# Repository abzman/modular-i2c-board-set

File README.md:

# modular-i2c-board-set
boards designed to be used together to create a modular control system

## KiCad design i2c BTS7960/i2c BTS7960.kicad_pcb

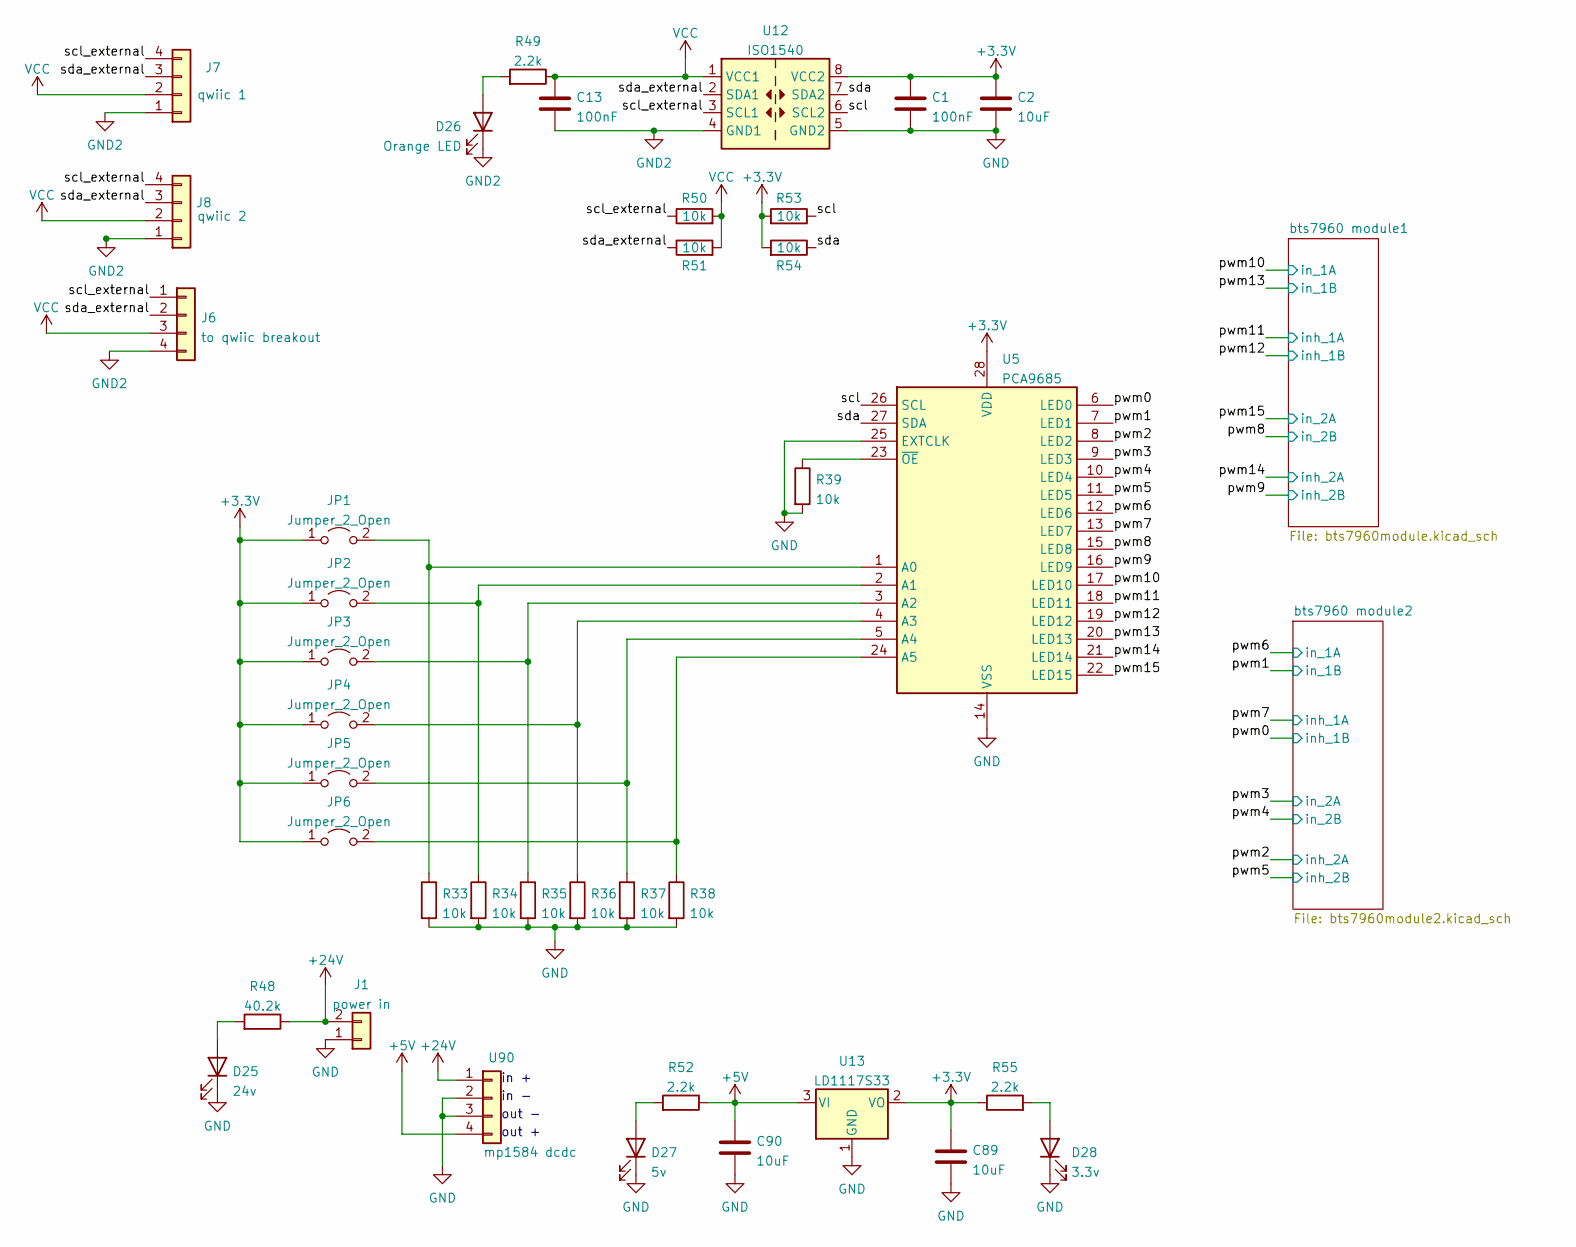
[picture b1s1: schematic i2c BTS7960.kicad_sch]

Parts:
C1, C13: 100nF; C_0603_1608Metric
C2: 10uF; C_0603_1608Metric
C89, C90: 10uF; C_1206_3216Metric
D25: 24v; LED_0603_1608Metric
D26: Orange LED; LED_0603_1608Metric
D27: 5v; LED_0603_1608Metric
D28: 3.3v; LED_0603_1608Metric
J1: power in; TerminalBlock_Phoenix_MKDS-1,5-2_1x02_P5.00mm_Horizontal
J6: to qwiic breakout; PinHeader_1x04_P2.54mm_Vertical
J7: qwiic 1; JST_SH_SM04B-SRSS-TB_1x04-1MP_P1.00mm_Horizontal
J8: qwiic 2; JST_SH_SM04B-SRSS-TB_1x04-1MP_P1.00mm_Horizontal
JP1, JP2, JP3, JP4, JP5: Jumper_2_Open; SolderJumper-2_P1.3mm_Open_RoundedPad1.0x1.5mm
JP6: Jumper_2_Open; SolderJumper-2_P1.3mm_Bridged_RoundedPad1.0x1.5mm
R33, R34, R35, R36, R37, R38, R39, R50, R51, R53, R54: 10k; R_0603_1608Metric
R48: 40.2k; R_0603_1608Metric
R49, R52, R55: 2.2k; R_0603_1608Metric
U5: PCA9685; TSSOP-28_4.4x9.7mm_P0.65mm
U12: ISO1540; SOIC-8_3.9x4.9mm_P1.27mm
U13: LD1117S33; SOT-223-3_TabPin2
U90: mp1584 dcdc; MP1584_buck_module

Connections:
+3V3: C1.1, C2.1, C89.1, JP1.1 (A), JP2.1 (A), JP3.1 (A), JP4.1 (A), JP5.1 (A), JP6.1 (A), R53.2, R54.2, R55.1, U5.28 (VDD), U12.8 (VCC2), U13.2 (VO)
+5V: C90.1, R52.1, U13.3 (VI), U90.4; also elsewhere on the board
+24V: J1.2, R48.1, U90.1; also elsewhere on the board
/pwm0: U5.6 (LED0); also elsewhere on the board
/pwm1: U5.7 (LED1); also elsewhere on the board
/pwm2: U5.8 (LED2); also elsewhere on the board
/pwm3: U5.9 (LED3); also elsewhere on the board
/pwm4: U5.10 (LED4); also elsewhere on the board
/pwm5: U5.11 (LED5); also elsewhere on the board
/pwm6: U5.12 (LED6); also elsewhere on the board
/pwm7: U5.13 (LED7); also elsewhere on the board
/pwm8: U5.15 (LED8); also elsewhere on the board
/pwm9: U5.16 (LED9); also elsewhere on the board
/pwm10: U5.17 (LED10); also elsewhere on the board
/pwm11: U5.18 (LED11); also elsewhere on the board
/pwm12: U5.19 (LED12); also elsewhere on the board
/pwm13: U5.20 (LED13); also elsewhere on the board
/pwm14: U5.21 (LED14); also elsewhere on the board
/pwm15: U5.22 (LED15); also elsewhere on the board
/scl: R53.1, U5.26 (SCL), U12.6 (SCL2)
/scl_external: J6.1, J7.4, J8.4, R50.1, U12.3 (SCL1)
/sda: R54.1, U5.27 (SDA), U12.7 (SDA2)
/sda_external: J6.2, J7.3, J8.3, R51.1, U12.2 (SDA1)
GND: C1.2, C2.2, C89.2, C90.2, D25.1 (K), D27.1 (K), D28.1 (K), J1.1, J7.MP, J8.MP, R33.2, R34.2, R35.2, R36.2, R37.2, R38.2, R39.2, U5.14 (VSS), U5.25 (EXTCLK), U12.5 (GND2), U13.1 (GND), U90.2, U90.3; also elsewhere on the board
GND2: C13.2, D26.1 (K), J6.4, J7.1, J8.1, U12.4 (GND1)
unnamed: D25.2 (A), R48.2
unnamed: D26.2 (A), R49.2
unnamed: D27.2 (A), R52.2
unnamed: D28.2 (A), R55.2
unnamed: JP1.2 (B), R33.1, U5.1 (A0)
unnamed: JP2.2 (B), R34.1, U5.2 (A1)
unnamed: JP3.2 (B), R35.1, U5.3 (A2)
unnamed: JP4.2 (B), R36.1, U5.4 (A3)
unnamed: JP5.2 (B), R37.1, U5.5 (A4)
unnamed: JP6.2 (B), R38.1, U5.24 (A5)
unnamed: R39.1, U5.23 (~OE)
VCC: C13.1, J6.3, J7.2, J8.2, R49.1, R50.2, R51.2, U12.1 (VCC1)

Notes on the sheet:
in +
out -
out +
in -

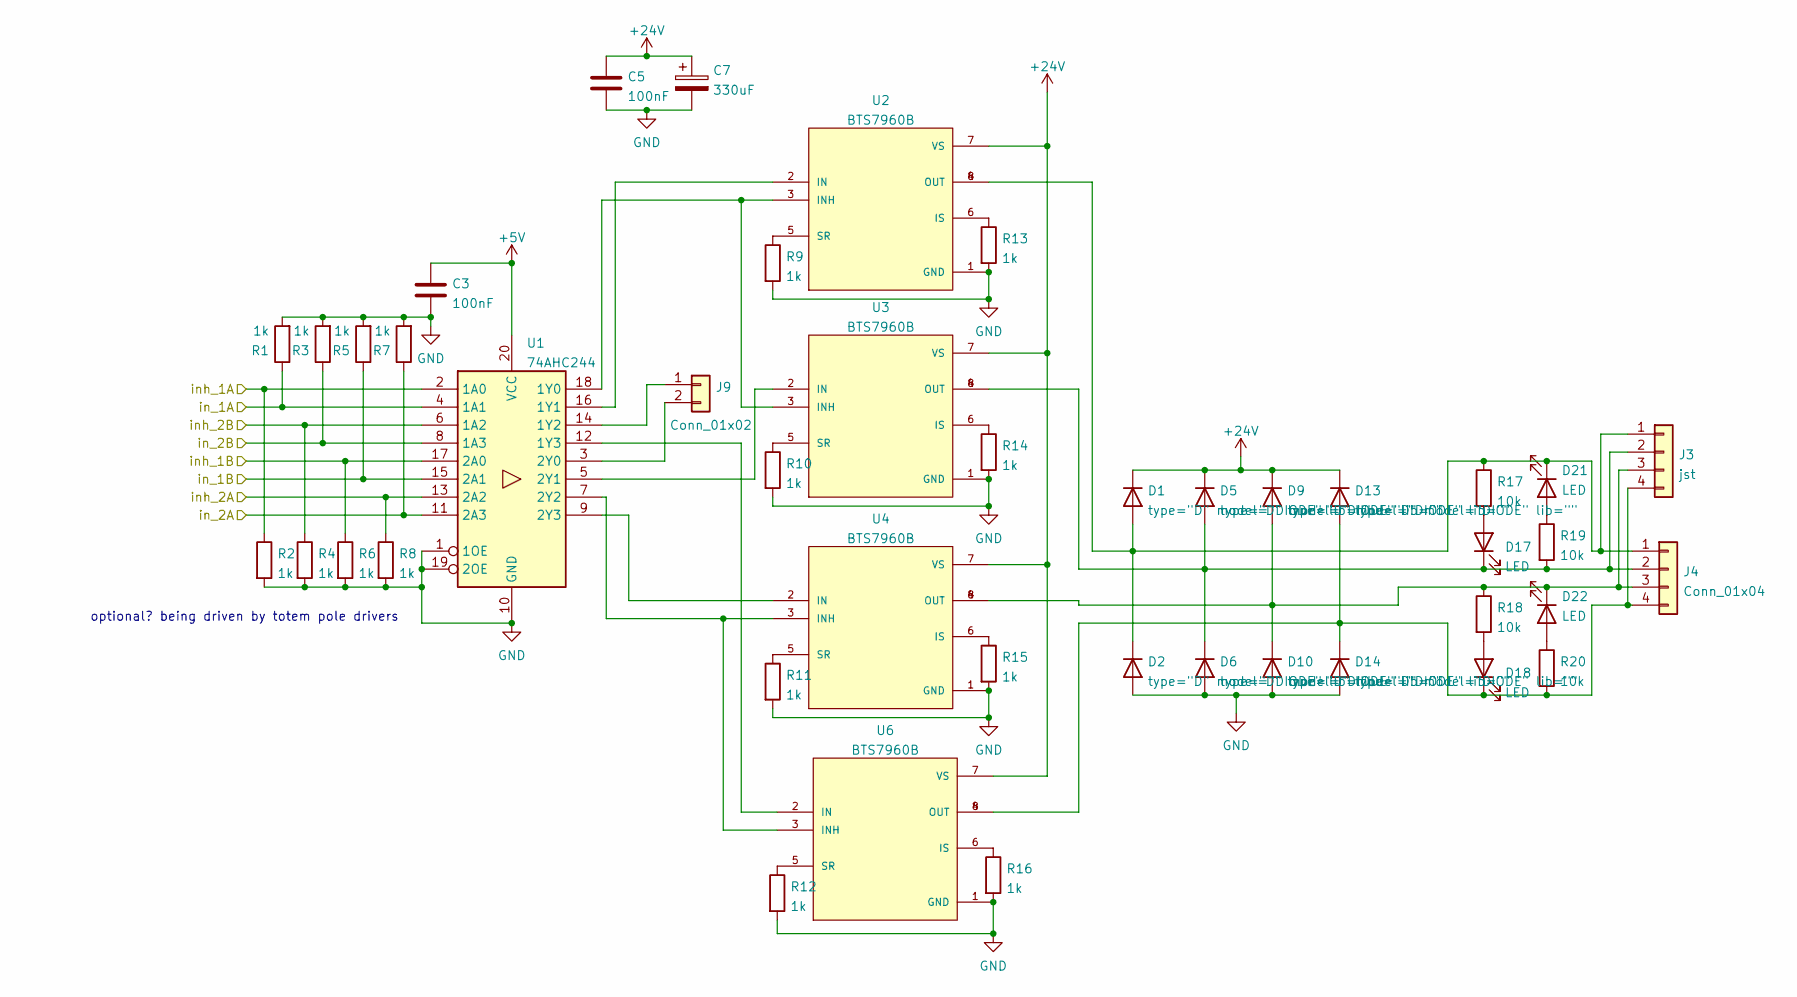
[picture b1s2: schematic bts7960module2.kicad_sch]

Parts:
C3, C5: 100nF; C_0603_1608Metric
C7: 330uF; CP_Radial_D10.0mm_P5.00mm
D1, D2, D5, D6, D9, D10, D13, D14: type="D" model="DIODE" lib=""; D_SMA
D17, D18, D21, D22: LED; LED_0603_1608Metric
J3: jst; JST_XH_B4B-XH-A_1x04_P2.50mm_Vertical
J4: Conn_01x04; TerminalBlock_Phoenix_MKDS-1,5-4_1x04_P5.00mm_Horizontal
J9: Conn_01x02; PinHeader_2x01_P2.54mm_Vertical
R1, R2, R3, R4, R5, R6, R7, R8, R9, R10, R11, R12, R13, R14, R15, R16: 1k; R_0603_1608Metric
R17, R18, R19, R20: 10k; R_0603_1608Metric
U1: 74AHC244; SOIC-20W_7.5x12.8mm_P1.27mm
U2, U3, U4, U6: BTS7960B; DPAK127P1490X440-8N; PARTREV 1.1

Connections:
+5V: C3.1, U1.20 (VCC); also elsewhere on the board
+24V: C5.1, C7.1, D1.2 (K), D5.2 (K), D9.2 (K), D13.2 (K), U2.7 (VS), U3.7 (VS), U4.7 (VS), U6.7 (VS); also elsewhere on the board
/pwm0: R6.1, U1.17 (2A0); also elsewhere on the board
/pwm1: R5.1, U1.15 (2A1); also elsewhere on the board
/pwm2: R8.1, U1.13 (2A2); also elsewhere on the board
/pwm3: R7.1, U1.11 (2A3); also elsewhere on the board
/pwm4: R3.1, U1.8 (1A3); also elsewhere on the board
/pwm5: R4.1, U1.6 (1A2); also elsewhere on the board
/pwm6: R1.1, U1.4 (1A1); also elsewhere on the board
/pwm7: R2.1, U1.2 (1A0); also elsewhere on the board
GND: C3.2, C5.2, C7.2, D2.1 (A), D6.1 (A), D10.1 (A), D14.1 (A), R1.2, R2.2, R3.2, R4.2, R5.2, R6.2, R7.2, R8.2, R9.2, R10.2, R11.2, R12.2, R13.2, R14.2, R15.2, R16.2, U1.1 (1OE), U1.10 (GND), U1.19 (2OE), U2.1 (GND), U3.1 (GND), U4.1 (GND), U6.1 (GND); also elsewhere on the board
unnamed: D1.1 (A), D2.2 (K), D21.1 (K), J3.1, J4.1, R17.1, U2.4 (OUT), U2.8 (OUT)
unnamed: D9.1 (A), D10.2 (K), D22.1 (K), J3.3, J4.3, R18.1, U4.4 (OUT), U4.8 (OUT)
unnamed: D13.1 (A), D14.2 (K), D18.1 (K), J3.4, J4.4, R20.2, U6.4 (OUT), U6.8 (OUT)
unnamed: D17.2 (A), R17.2
unnamed: D5.1 (A), D6.2 (K), D17.1 (K), J3.2, J4.2, R19.2, U3.4 (OUT), U3.8 (OUT)
unnamed: D18.2 (A), R18.2
unnamed: D21.2 (A), R19.1
unnamed: D22.2 (A), R20.1
unnamed: J9.1, U1.14 (1Y2)
unnamed: J9.2, U1.3 (2Y0)
unnamed: U1.18 (1Y0), U2.3 (INH), U3.3 (INH)
unnamed: U1.16 (1Y1), U2.2 (IN)
unnamed: U1.12 (1Y3), U6.2 (IN)
unnamed: U1.5 (2Y1), U3.2 (IN)
unnamed: U1.7 (2Y2), U4.3 (INH), U6.3 (INH)
unnamed: U1.9 (2Y3), U4.2 (IN)
unnamed: R13.1, U2.6 (IS)
unnamed: R9.1, U2.5 (SR)
unnamed: R14.1, U3.6 (IS)
unnamed: R10.1, U3.5 (SR)
unnamed: R15.1, U4.6 (IS)
unnamed: R11.1, U4.5 (SR)
unnamed: R16.1, U6.6 (IS)
unnamed: R12.1, U6.5 (SR)

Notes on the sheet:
optional? being driven by totem pole drivers

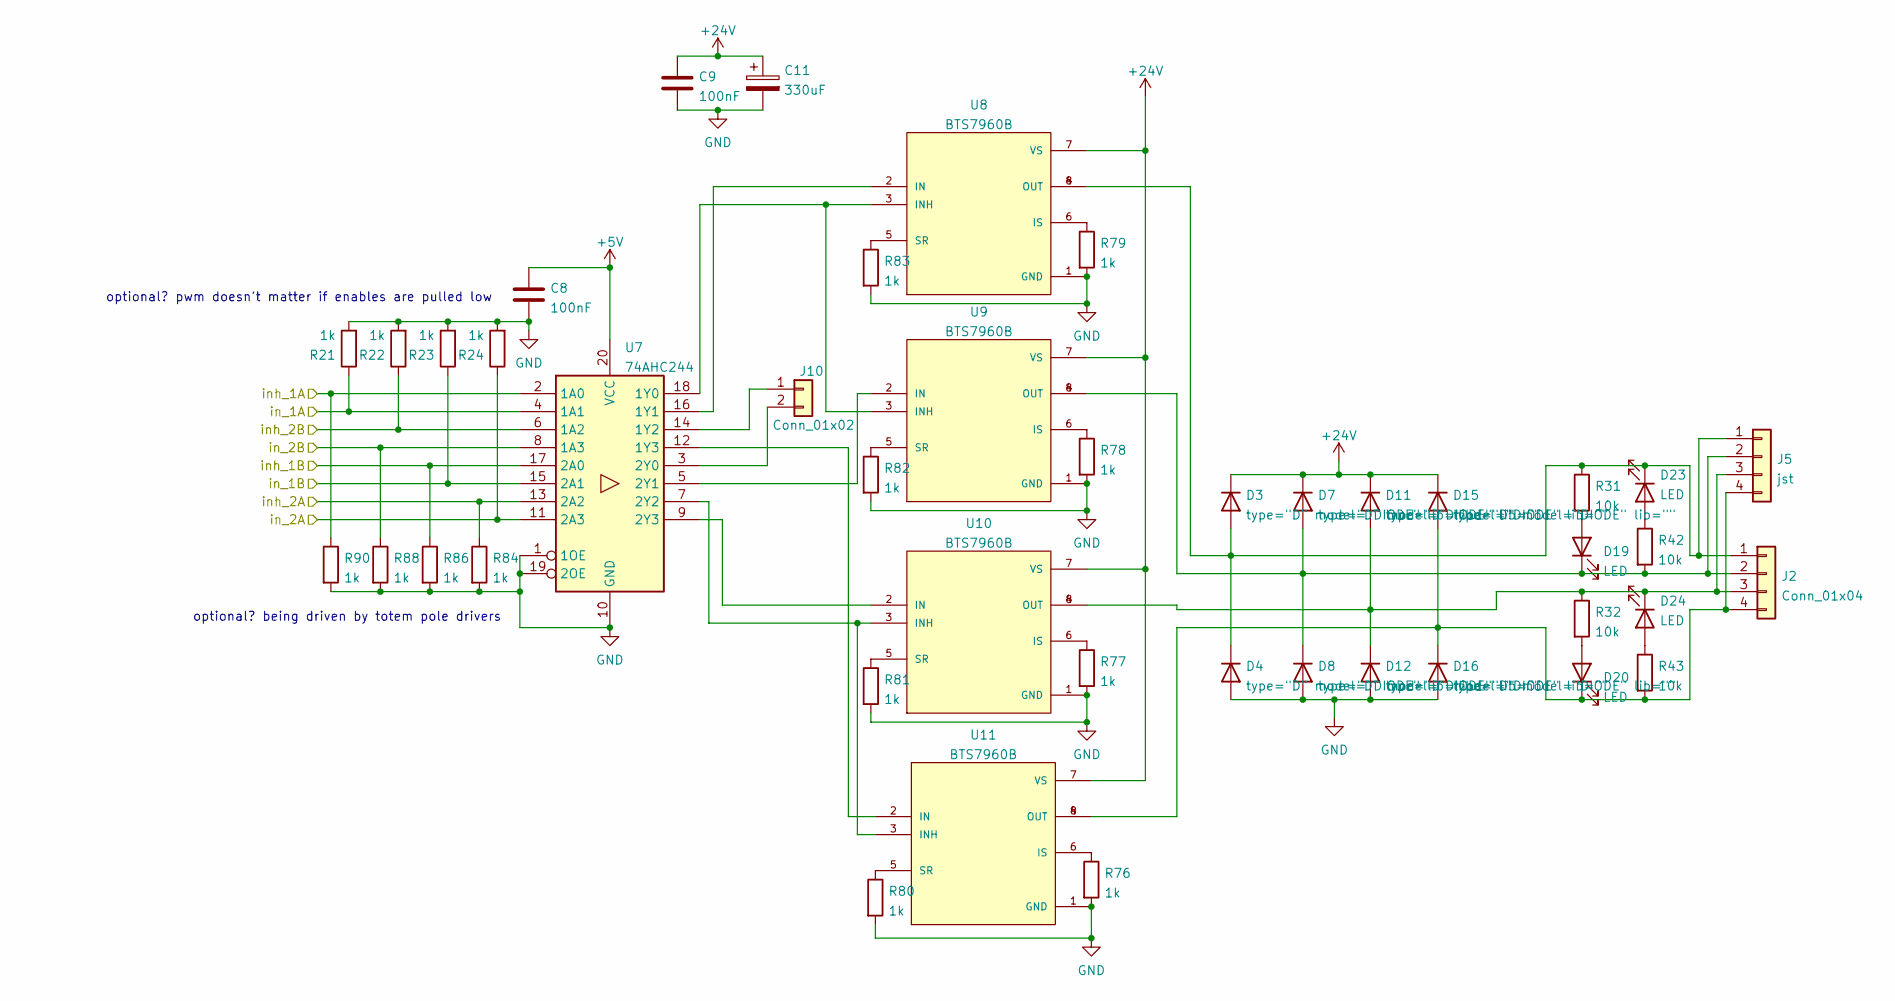
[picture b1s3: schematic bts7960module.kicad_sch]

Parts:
C8, C9: 100nF; C_0603_1608Metric
C11: 330uF; CP_Radial_D10.0mm_P5.00mm
D3, D4, D7, D8, D11, D12, D15, D16: type="D" model="DIODE" lib=""; D_SMA
D19, D20, D23, D24: LED; LED_0603_1608Metric
J2: Conn_01x04; TerminalBlock_Phoenix_MKDS-1,5-4_1x04_P5.00mm_Horizontal
J5: jst; JST_XH_B4B-XH-A_1x04_P2.50mm_Vertical
J10: Conn_01x02; PinHeader_2x01_P2.54mm_Vertical
R21, R22, R23, R24, R76, R77, R78, R79, R80, R81, R82, R83, R84, R86, R88, R90: 1k; R_0603_1608Metric
R31, R32, R42, R43: 10k; R_0603_1608Metric
U7: 74AHC244; SOIC-20W_7.5x12.8mm_P1.27mm
U8, U9, U10, U11: BTS7960B; DPAK127P1490X440-8N; PARTREV 1.1

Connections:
+5V: C8.1, U7.20 (VCC); also elsewhere on the board
+24V: C9.1, C11.1, D3.2 (K), D7.2 (K), D11.2 (K), D15.2 (K), U8.7 (VS), U9.7 (VS), U10.7 (VS), U11.7 (VS); also elsewhere on the board
/pwm8: R88.1, U7.8 (1A3); also elsewhere on the board
/pwm9: R22.1, U7.6 (1A2); also elsewhere on the board
/pwm10: R21.1, U7.4 (1A1); also elsewhere on the board
/pwm11: R90.1, U7.2 (1A0); also elsewhere on the board
/pwm12: R86.1, U7.17 (2A0); also elsewhere on the board
/pwm13: R23.1, U7.15 (2A1); also elsewhere on the board
/pwm14: R84.1, U7.13 (2A2); also elsewhere on the board
/pwm15: R24.1, U7.11 (2A3); also elsewhere on the board
GND: C8.2, C9.2, C11.2, D4.1 (A), D8.1 (A), D12.1 (A), D16.1 (A), R21.2, R22.2, R23.2, R24.2, R76.2, R77.2, R78.2, R79.2, R80.2, R81.2, R82.2, R83.2, R84.2, R86.2, R88.2, R90.2, U7.1 (1OE), U7.10 (GND), U7.19 (2OE), U8.1 (GND), U9.1 (GND), U10.1 (GND), U11.1 (GND); also elsewhere on the board
unnamed: D11.1 (A), D12.2 (K), D24.1 (K), J2.3, J5.3, R32.1, U10.4 (OUT), U10.8 (OUT)
unnamed: D15.1 (A), D16.2 (K), D20.1 (K), J2.4, J5.4, R43.2, U11.4 (OUT), U11.8 (OUT)
unnamed: D19.2 (A), R31.2
unnamed: D7.1 (A), D8.2 (K), D19.1 (K), J2.2, J5.2, R42.2, U9.4 (OUT), U9.8 (OUT)
unnamed: D20.2 (A), R32.2
unnamed: D23.2 (A), R42.1
unnamed: D3.1 (A), D4.2 (K), D23.1 (K), J2.1, J5.1, R31.1, U8.4 (OUT), U8.8 (OUT)
unnamed: D24.2 (A), R43.1
unnamed: J10.1, U7.14 (1Y2)
unnamed: J10.2, U7.3 (2Y0)
unnamed: U7.18 (1Y0), U8.3 (INH), U9.3 (INH)
unnamed: U7.16 (1Y1), U8.2 (IN)
unnamed: U7.5 (2Y1), U9.2 (IN)
unnamed: R79.1, U8.6 (IS)
unnamed: R83.1, U8.5 (SR)
unnamed: R78.1, U9.6 (IS)
unnamed: R82.1, U9.5 (SR)
unnamed: U7.9 (2Y3), U10.2 (IN)
unnamed: U7.7 (2Y2), U10.3 (INH), U11.3 (INH)
unnamed: R77.1, U10.6 (IS)
unnamed: R81.1, U10.5 (SR)
unnamed: U7.12 (1Y3), U11.2 (IN)
unnamed: R76.1, U11.6 (IS)
unnamed: R80.1, U11.5 (SR)

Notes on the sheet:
optional? pwm doesn't matter if enables are pulled low
optional? being driven by totem pole drivers

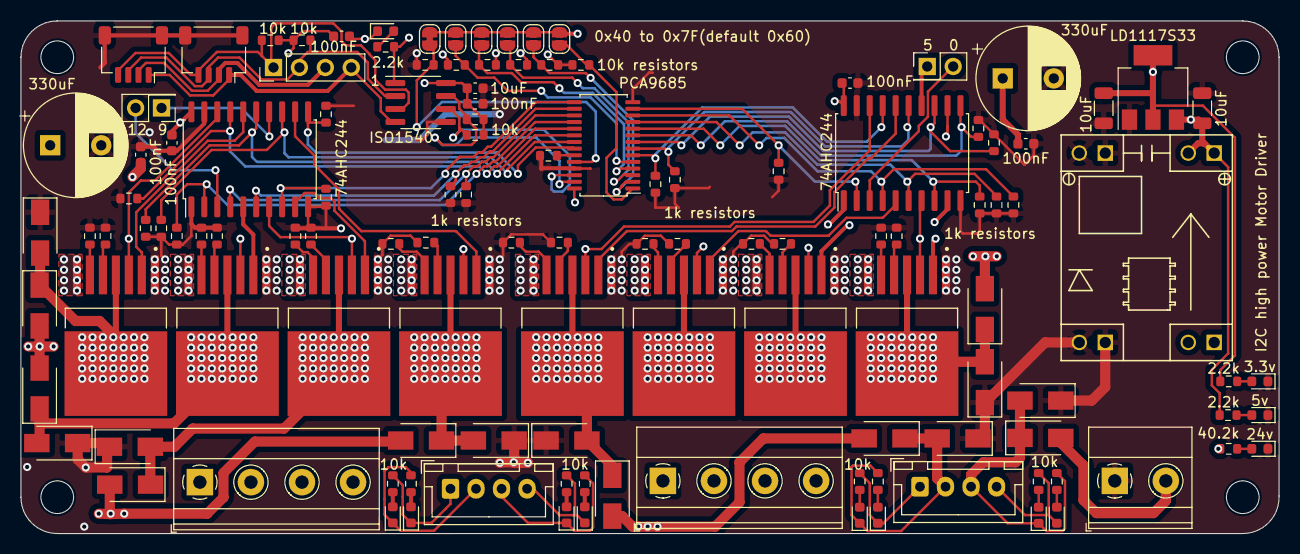
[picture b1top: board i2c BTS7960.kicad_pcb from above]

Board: 4 copper layers, 123.2 x 50.2 mm, 124 parts (0 on the bottom side), 85 nets.

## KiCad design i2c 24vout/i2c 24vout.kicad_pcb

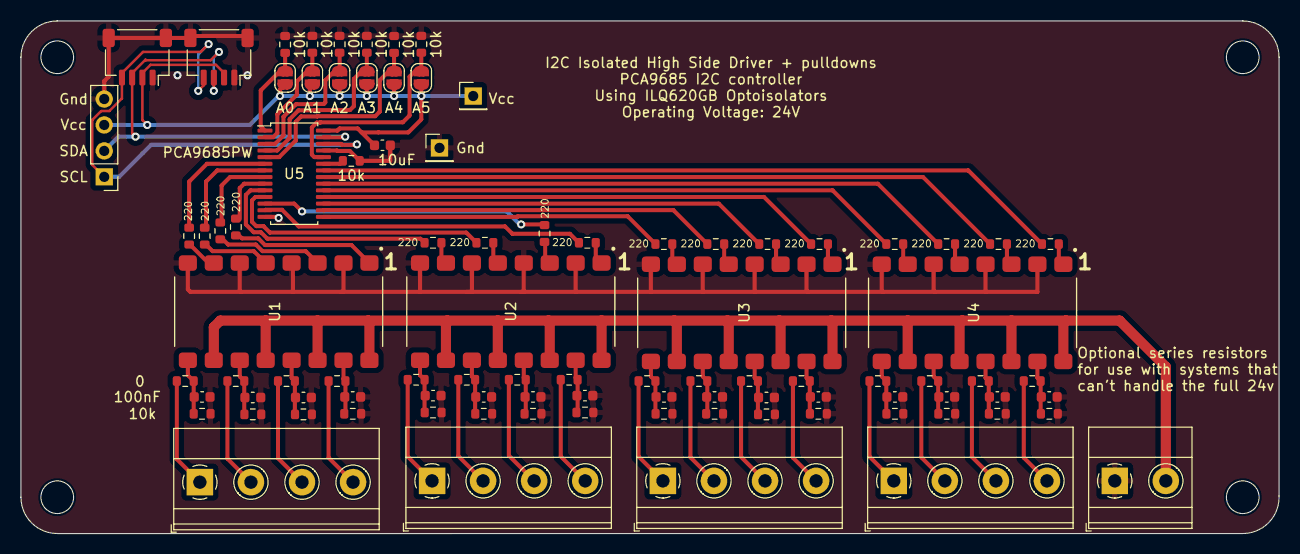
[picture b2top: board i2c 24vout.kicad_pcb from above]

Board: 2 copper layers, 123.2 x 50.2 mm, 93 parts (0 on the bottom side), 76 nets.

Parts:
C1, C2, C3, C4, C5, C6, C7, C8, C9, C10, C11, C12, C13, C14, C15, C16: 100nF; C_0603_1608Metric
C17: 10uF; C_0603_1608Metric
J1: power in; TerminalBlock_Phoenix_MKDS-1,5-2_1x02_P5.00mm_Horizontal
J2, J3, J4, J5: Conn_01x04; TerminalBlock_Phoenix_MKDS-1,5-4_1x04_P5.00mm_Horizontal
J6: to qwiic breakout; PinHeader_1x04_P2.54mm_Vertical
J7: qwiic 1; JST_SH_SM04B-SRSS-TB_1x04-1MP_P1.00mm_Horizontal
J8: qwiic 2; JST_SH_SM04B-SRSS-TB_1x04-1MP_P1.00mm_Horizontal
J9, J10: Conn_01x01; PinHeader_1x01_P2.54mm_Vertical
JP1, JP2, JP3, JP4, JP5, JP6: Jumper_2_Open; SolderJumper-2_P1.3mm_Open_RoundedPad1.0x1.5mm
R1, R2, R3, R4, R5, R6, R7, R8, R9, R10, R11, R12, R13, R14, R15, R16: 220; R_0603_1608Metric
R17, R18, R19, R20, R21, R22, R23, R24, R25, R26, R27, R28, R29, R30, R31, R32, R33, R34, R35, R36, R37, R38, R39: 10k; R_0603_1608Metric
R40, R41, R42, R43, R44, R45, R46, R47, R48, R49, R50, R51, R52, R53, R54, R55: 0; R_0603_1608Metric
U1, U2, U3, U4: ILQ620GB-X009; OPTO_ILQ620GB-X009
U5: PCA9685PW; TSSOP-28_4.4x9.7mm_P0.65mm

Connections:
+24V: J1.2, U1.10, U1.12, U1.14, U1.16, U2.10, U2.12, U2.14, U2.16, U3.10, U3.12, U3.14, U3.16, U4.10, U4.12, U4.14, U4.16
/pwm0: R1.2, U5.6 (LED0)
/pwm1: R2.2, U5.7 (LED1)
/pwm2: R3.2, U5.8 (LED2)
/pwm3: R4.2, U5.9 (LED3)
/pwm4: R5.2, U5.10 (LED4)
/pwm5: R6.2, U5.11 (LED5)
/pwm6: R7.2, U5.12 (LED6)
/pwm7: R8.2, U5.13 (LED7)
/pwm8: R9.2, U5.15 (LED8)
/pwm9: R10.2, U5.16 (LED9)
/pwm10: R11.2, U5.17 (LED10)
/pwm11: R12.2, U5.18 (LED11)
/pwm12: R13.2, U5.19 (LED12)
/pwm13: R14.2, U5.20 (LED13)
/pwm14: R15.2, U5.21 (LED14)
/pwm15: R16.2, U5.22 (LED15)
/scl: J6.1, J7.4, J8.4, U5.26 (SCL)
/sda: J6.2, J7.3, J8.3, U5.27 (SDA)
GND: C1.2, C2.2, C3.2, C4.2, C5.2, C6.2, C7.2, C8.2, C9.2, C10.2, C11.2, C12.2, C13.2, C14.2, C15.2, C16.2, C17.2, J1.1, J6.4, J7.1, J7.MP, J8.1, J8.MP, J10.1, R17.2, R18.2, R19.2, R20.2, R21.2, R22.2, R23.2, R24.2, R25.2, R26.2, R27.2, R28.2, R29.2, R30.2, R31.2, R32.2, R33.2, R34.2, R35.2, R36.2, R37.2, R38.2, R39.2, U1.2, U1.4, U1.6, U1.8, U2.2, U2.4, U2.6, U2.8, U3.2, U3.4, U3.6, U3.8, U4.2, U4.4, U4.6, U4.8, U5.14 (VSS), U5.25 (EXTCLK)
unnamed: C1.1, R17.1, R40.1, U1.9
unnamed: C2.1, R18.1, R41.1, U1.11
unnamed: C3.1, R19.1, R42.1, U1.13
unnamed: C4.1, R20.1, R43.1, U1.15
unnamed: C5.1, R21.1, R44.1, U2.9
unnamed: C6.1, R22.1, R45.1, U2.11
unnamed: C7.1, R23.1, R46.1, U2.13
unnamed: C8.1, R24.1, R47.1, U2.15
unnamed: C9.1, R25.1, R48.1, U3.9
unnamed: C10.1, R26.1, R49.1, U3.11
unnamed: C11.1, R27.1, R50.1, U3.13
unnamed: C12.1, R28.1, R51.1, U3.15
unnamed: C13.1, R29.1, R52.1, U4.9
unnamed: C14.1, R30.1, R53.1, U4.11
unnamed: C15.1, R31.1, R54.1, U4.13
unnamed: C16.1, R32.1, R55.1, U4.15
unnamed: J2.1, R40.2
unnamed: J2.2, R41.2
unnamed: J2.3, R42.2
unnamed: J2.4, R43.2
unnamed: J3.1, R44.2
unnamed: J3.2, R45.2
unnamed: J3.3, R46.2
unnamed: J3.4, R47.2
unnamed: J4.1, R48.2
unnamed: J4.2, R49.2
unnamed: J4.3, R50.2
unnamed: J4.4, R51.2
unnamed: J5.1, R52.2
unnamed: J5.2, R53.2
unnamed: J5.3, R54.2
unnamed: J5.4, R55.2
unnamed: JP1.2 (B), R33.1, U5.1 (A0)
unnamed: JP2.2 (B), R34.1, U5.2 (A1)
unnamed: JP3.2 (B), R35.1, U5.3 (A2)
unnamed: JP4.2 (B), R36.1, U5.4 (A3)
unnamed: JP5.2 (B), R37.1, U5.5 (A4)
unnamed: JP6.2 (B), R38.1, U5.24 (A5)
unnamed: R1.1, U1.7
unnamed: R2.1, U1.5
unnamed: R3.1, U1.3
unnamed: R4.1, U1.1
unnamed: R5.1, U2.7
unnamed: R6.1, U2.5
unnamed: R7.1, U2.3
unnamed: R8.1, U2.1
unnamed: R9.1, U3.7
unnamed: R10.1, U3.5
unnamed: R11.1, U3.3
unnamed: R12.1, U3.1
unnamed: R13.1, U4.7
unnamed: R14.1, U4.5
unnamed: R15.1, U4.3
unnamed: R16.1, U4.1
unnamed: R39.1, U5.23 (~OE)
VCC: C17.1, J6.3, J7.2, J8.2, J9.1, JP1.1 (A), JP2.1 (A), JP3.1 (A), JP4.1 (A), JP5.1 (A), JP6.1 (A), U5.28 (VDD)

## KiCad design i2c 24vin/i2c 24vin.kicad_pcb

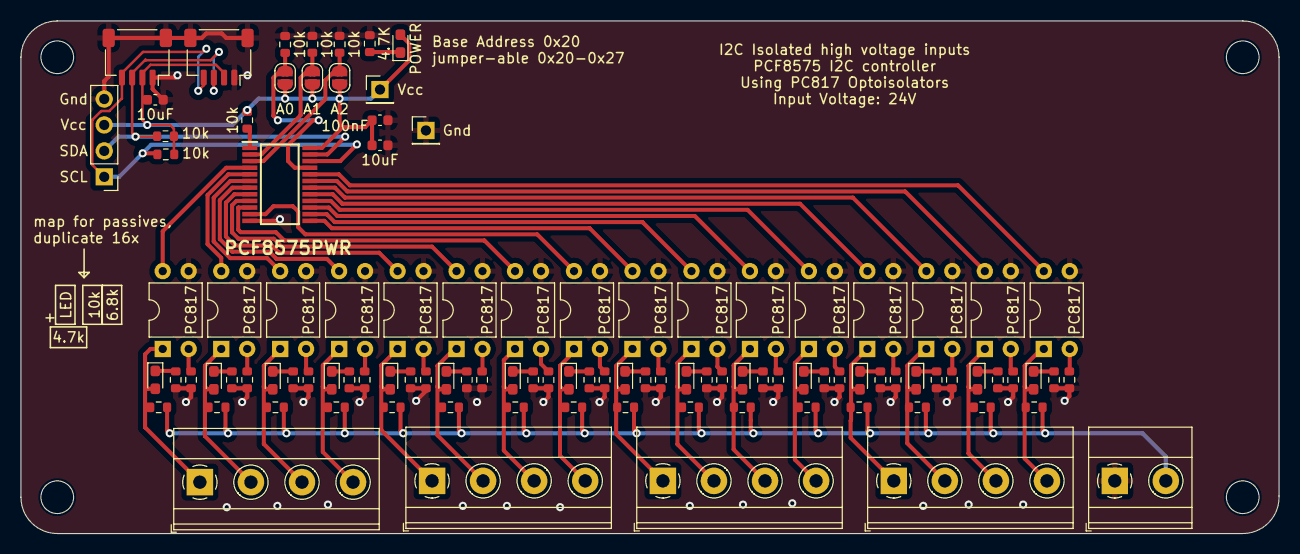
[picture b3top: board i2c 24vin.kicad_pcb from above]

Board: 2 copper layers, 123.2 x 50.2 mm, 105 parts (0 on the bottom side), 74 nets.

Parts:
C1, C3: 10uF; C_0603_1608Metric
C2: 100nF; C_0603_1608Metric
D1: POWER; LED_0603_1608Metric_Pad1.05x0.95mm_HandSolder
D2, D3, D4, D5, D6, D7, D8, D9, D10, D11, D12, D13, D14, D15, D16, D17: LED; LED_0603_1608Metric_Pad1.05x0.95mm_HandSolder
IC1: PCF8575PWR; SOP65P640X120-24N
J1, J2, J3, J4: Conn_01x04; TerminalBlock_Phoenix_MKDS-1,5-4_1x04_P5.00mm_Horizontal
J5, J6: Conn_01x01; PinHeader_1x01_P2.54mm_Vertical
J7: qwiic 1; JST_SH_SM04B-SRSS-TB_1x04-1MP_P1.00mm_Horizontal
J8: qwiic 2; JST_SH_SM04B-SRSS-TB_1x04-1MP_P1.00mm_Horizontal
J9: i2c test points; PinHeader_1x04_P2.54mm_Vertical
J10: power in; TerminalBlock_Phoenix_MKDS-1,5-2_1x02_P5.00mm_Horizontal
JP1, JP2, JP3: Jumper_2_Open; SolderJumper-2_P1.3mm_Open_RoundedPad1.0x1.5mm
R1: 4.7K; R_0603_1608Metric
R2, R3, R4, R5, R6, R7, R8, R10, R12, R14, R16, R18, R20, R22, R24, R26, R28, R30, R32, R34, R36, R38: 10k; R_0603_1608Metric
R9, R11, R13, R15, R17, R19, R21, R23, R25, R27, R29, R31, R33, R35, R37, R39: 6.8k; R_0603_1608Metric
R40, R41, R42, R43, R44, R45, R46, R47, R48, R49, R50, R51, R52, R53, R54, R55: 4.7k; R_0603_1608Metric
U1, U2, U3, U4, U5, U6, U7, U8, U9, U10, U11, U12, U13, U14, U15, U16: PC817; DIP-4_W7.62mm

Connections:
+24V: J10.2, R40.1, R41.1, R42.1, R43.1, R44.1, R45.1, R46.1, R47.1, R48.1, R49.1, R50.1, R51.1, R52.1, R53.1, R54.1, R55.1
/Single Channel opto-isolator circuit1/Input: D3.2 (A), J1.1, R41.2, U2.1
/Single Channel opto-isolator circuit2/Input: D4.2 (A), J1.2, R42.2, U3.1
/Single Channel opto-isolator circuit3/Input: D5.2 (A), J1.3, R43.2, U4.1
/Single Channel opto-isolator circuit4/Input: D6.2 (A), J1.4, R44.2, U5.1
/Single Channel opto-isolator circuit5/Input: D7.2 (A), J2.2, R45.2, U6.1
/Single Channel opto-isolator circuit6/Input: D8.2 (A), J2.3, R46.2, U7.1
/Single Channel opto-isolator circuit7/Input: D9.2 (A), J2.4, R47.2, U8.1
/Single Channel opto-isolator circuit8/Input: D11.2 (A), J3.1, R49.2, U10.1
/Single Channel opto-isolator circuit9/Input: D12.2 (A), J3.2, R50.2, U11.1
/Single Channel opto-isolator circuit10/Input: D13.2 (A), J3.3, R51.2, U12.1
/Single Channel opto-isolator circuit11/Input: D14.2 (A), J3.4, R52.2, U13.1
/Single Channel opto-isolator circuit12/Input: D10.2 (A), J4.1, R48.2, U9.1
/Single Channel opto-isolator circuit13/Input: D15.2 (A), J4.2, R53.2, U14.1
/Single Channel opto-isolator circuit14/Input: D16.2 (A), J4.3, R54.2, U15.1
/Single Channel opto-isolator circuit15/Input: D17.2 (A), J4.4, R55.2, U16.1
/Single Channel opto-isolator circuit/Input: D2.2 (A), J2.1, R40.2, U1.1
/scl: IC1.22 (SCL), J7.4, J8.4, J9.1, R6.2
/sda: IC1.23 (SDA), J7.3, J8.3, J9.2, R7.2
A0: IC1.21 (A0), JP1.2 (B), R2.1
A1: IC1.2 (A1), JP2.2 (B), R3.1
A2: IC1.3 (A2), JP3.2 (B), R4.1
GND: C1.2, C2.2, C3.2, IC1.12 (GND), J6.1, J7.1, J7.MP, J8.1, J8.MP, J9.4, J10.1, R1.2, R2.2, R3.2, R4.2, R8.2, R9.2, R10.2, R11.2, R12.2, R13.2, R14.2, R15.2, R16.2, R17.2, R18.2, R19.2, R20.2, R21.2, R22.2, R23.2, R24.2, R25.2, R26.2, R27.2, R28.2, R29.2, R30.2, R31.2, R32.2, R33.2, R34.2, R35.2, R36.2, R37.2, R38.2, R39.2, U1.3, U2.3, U3.3, U4.3, U5.3, U6.3, U7.3, U8.3, U9.3, U10.3, U11.3, U12.3, U13.3, U14.3, U15.3, U16.3
unnamed: D1.1 (K), R1.1
unnamed: D2.1 (K), R8.1
unnamed: D3.1 (K), R10.1
unnamed: D4.1 (K), R12.1
unnamed: D5.1 (K), R14.1
unnamed: D6.1 (K), R16.1
unnamed: D7.1 (K), R18.1
unnamed: D8.1 (K), R20.1
unnamed: D9.1 (K), R22.1
unnamed: D10.1 (K), R24.1
unnamed: D11.1 (K), R26.1
unnamed: D12.1 (K), R28.1
unnamed: D13.1 (K), R30.1
unnamed: D14.1 (K), R32.1
unnamed: D15.1 (K), R34.1
unnamed: D16.1 (K), R36.1
unnamed: D17.1 (K), R38.1
unnamed: IC1.1 (~INT), R5.2
unnamed: R9.1, U1.2
unnamed: R11.1, U2.2
unnamed: R13.1, U3.2
unnamed: R15.1, U4.2
unnamed: R17.1, U5.2
unnamed: R19.1, U6.2
unnamed: R21.1, U7.2
unnamed: R23.1, U8.2
unnamed: R25.1, U9.2
unnamed: R27.1, U10.2
unnamed: R29.1, U11.2
unnamed: R31.1, U12.2
unnamed: R33.1, U13.2
unnamed: R35.1, U14.2
unnamed: R37.1, U15.2
unnamed: R39.1, U16.2
VCC: C1.1, C2.1, C3.1, D1.2 (A), IC1.24 (VCC), J5.1, J7.2, J8.2, J9.3, JP1.1 (A), JP2.1 (A), JP3.1 (A), R5.1, R6.1, R7.1
input0: IC1.4 (P00), U2.4
input1: IC1.5 (P01), U3.4
input2: IC1.6 (P02), U4.4
input3: IC1.7 (P03), U5.4
input4: IC1.8 (P04), U1.4
input5: IC1.9 (P05), U6.4
input6: IC1.10 (P06), U7.4
input7: IC1.11 (P07), U8.4
input8: IC1.13 (P10), U10.4
input9: IC1.14 (P11), U11.4
input10: IC1.15 (P12), U12.4
input11: IC1.16 (P13), U13.4
input12: IC1.17 (P14), U9.4
input13: IC1.18 (P15), U14.4
input14: IC1.19 (P16), U15.4
input15: IC1.20 (P17), U16.4

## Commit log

2023-11-03 moved contents from other repo
    https://github.com/abzman/small-useful-PCBs
2023-11-03 added final libraries
2024-01-18 tweaked files
2024-04-10 DFM 24vin
2024-04-10 DFM 24vout
2024-04-11 motor controller DFM
